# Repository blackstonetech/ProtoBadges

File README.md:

# ProtoBadges

AutoDesk Eagle to Work with Files (You don't have to pay, use the free version)
https://www.autodesk.com/products/eagle/free-download

How to Eagle
https://www.autodesk.com/products/eagle/learning-center

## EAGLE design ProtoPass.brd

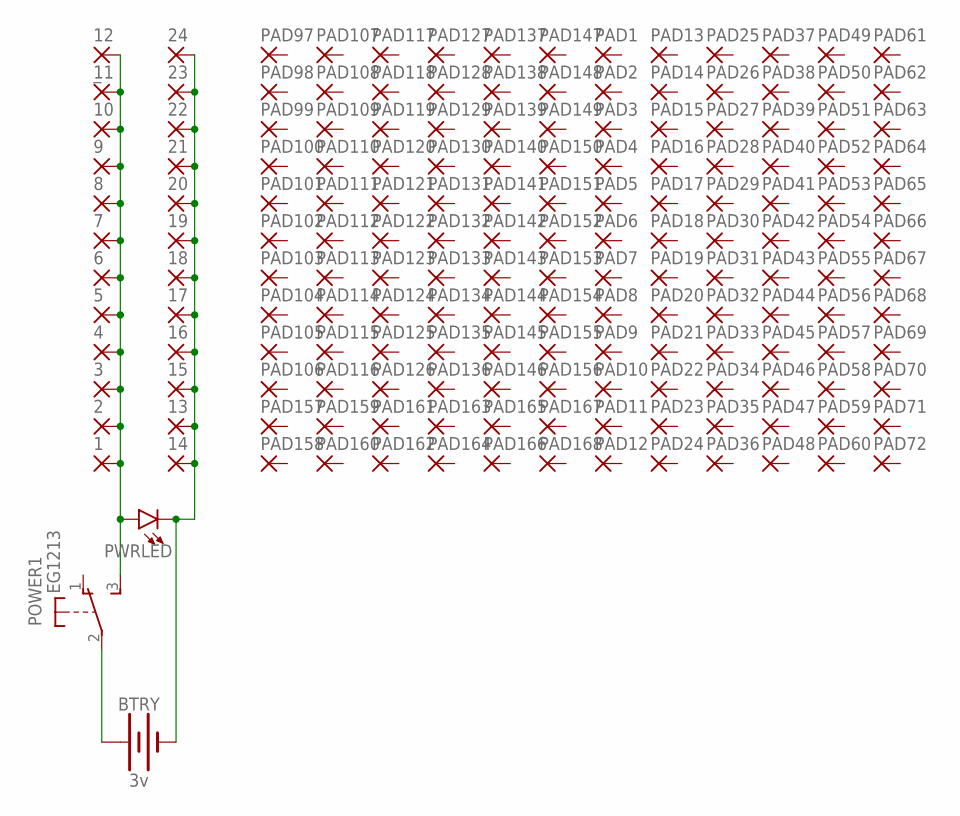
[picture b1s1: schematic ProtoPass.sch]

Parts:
1, 2, 3, 4, 5, 6, 7, 8, 9, 10, 11, 13, 14, 15, 16, 17, 18, 19, 20, 21, 22, 23, 24: 1,6/0,9
12: _; 1,6/0,9
BTRY: 3v; BATTCON_20MM_4LEGS_OVERPASTE
PAD1, PAD2, PAD3, PAD4, PAD5, PAD6, PAD7, PAD8, PAD9, PAD10, PAD11, PAD12, PAD13, PAD14, PAD15, PAD16, PAD17, PAD18, PAD19, PAD20, PAD21, PAD22, PAD23, PAD24, PAD25, PAD26, PAD27, PAD28, PAD29, PAD30, PAD31, PAD32, PAD33, PAD34, PAD35, PAD36, PAD37, PAD38, PAD39, PAD40, PAD41, PAD42, PAD43, PAD44, PAD45, PAD46, PAD47, PAD48, PAD49, PAD50, PAD51, PAD52, PAD53, PAD54, PAD55, PAD56, PAD57, PAD58, PAD59, PAD60, PAD61, PAD62, PAD63, PAD64, PAD65, PAD66, PAD67, PAD68, PAD69, PAD70, PAD71, PAD72, PAD97, PAD98, PAD99, PAD100, PAD101, PAD102, PAD103, PAD104, PAD105, PAD106, PAD107, PAD108, PAD109, PAD110, PAD111, PAD112, PAD113, PAD114, PAD115, PAD116, PAD117, PAD118, PAD119, PAD120, PAD121, PAD122, PAD123, PAD124, PAD125, PAD126, PAD127, PAD128, PAD129, PAD130, PAD131, PAD132, PAD133, PAD134, PAD135, PAD136, PAD137, PAD138, PAD139, PAD140, PAD141, PAD142, PAD143, PAD144, PAD145, PAD146, PAD147, PAD148, PAD149, PAD150, PAD151, PAD152, PAD153, PAD154, PAD155, PAD156, PAD157, PAD158, PAD159, PAD160, PAD161, PAD162, PAD163, PAD164, PAD165, PAD166, PAD167, PAD168: 1,6/0,9
POWER: EG1213
PWRLED: LED5MM; LED_5MM

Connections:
unnamed: 13.1, 14.1, 15.1, 16.1, 17.1, 18.1, 19.1, 20.1, 21.1, 22.1, 23.1, 24.1, BTRY.2 (-), PWRLED.K (C)
unnamed: BTRY.1 (+), POWER.2
unnamed: 1.1, 2.1, 3.1, 4.1, 5.1, 6.1, 7.1, 8.1, 9.1, 10.1, 11.1, 12.1, POWER.3 (S), PWRLED.A

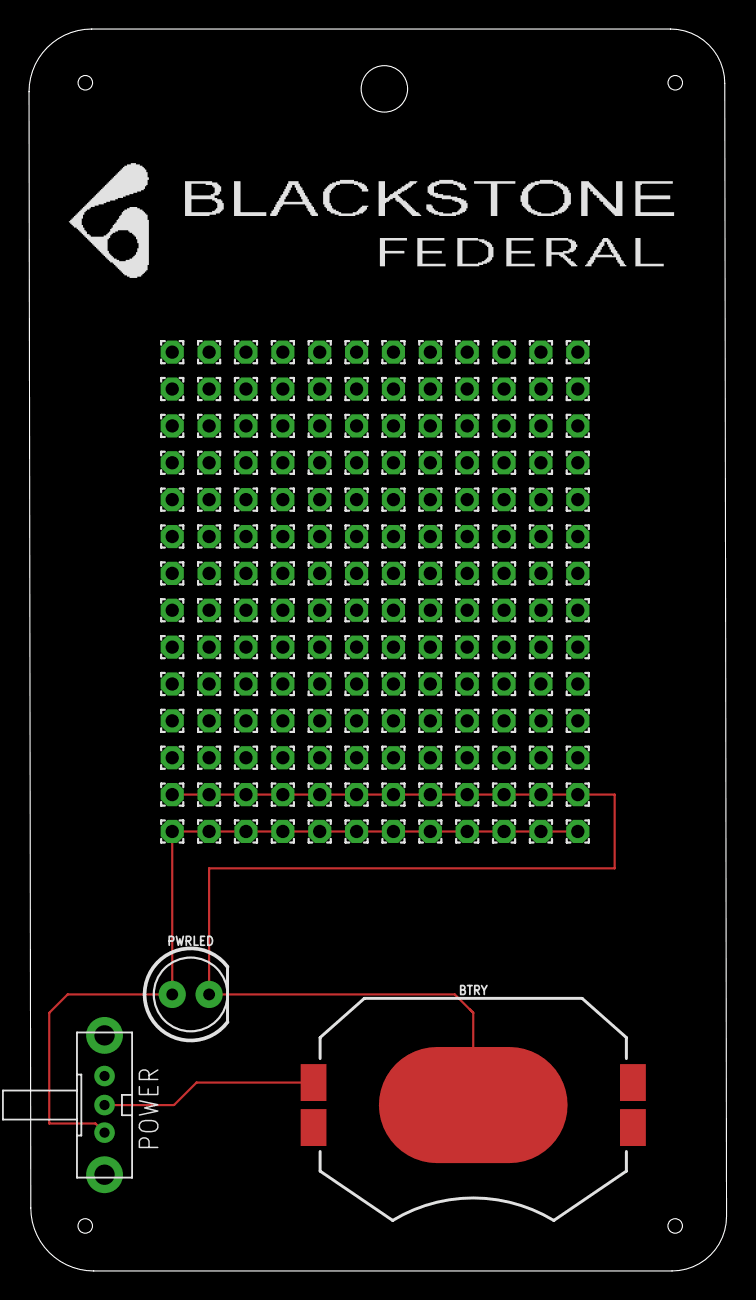
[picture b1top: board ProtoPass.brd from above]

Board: 2 copper layers, 48.1 x 85.6 mm, 171 parts (0 on the bottom side), 3 nets.

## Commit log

2018-06-21 Initial Commit of Protoboard 1.0

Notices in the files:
parts and their libraries:
SparkFun-LED: Licensing: Creative Commons ShareAlike 4.0 International - https://creativecommons.org/licenses/by-sa/4.0
